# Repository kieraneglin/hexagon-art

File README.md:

# Hexagon Art Piece

Because I'm incapable of saying no to ideas that sound fun

## What is it?

Many tightly packed wooden hexagons, each one driven linearly by its own stepper motor through a scotch yoke, creating a moving effect across the whole piece. A central orchestrator choreographs all of them together over a one-way UART bus.

```
Orchestrator (Raspberry Pi) --UART--> Distributor board --+--> Hexagon unit
                                                            +--> Hexagon unit
                                                            +--> ... (daisy-chained)
```

Each hexagon is a small standalone board: an ATtiny1616, a stepper driver, and an optical endstop for homing. The orchestrator broadcasts movement commands down the bus; units never talk back.

## Why is it?

A local art exhibit asked a communal woodshop that I am part of to create some installations. We were given no requirements other than being told that the theme is "art on the move". I took that extremely literally and this is what I came up with!

## Repository layout

- [`Firmware/`](Firmware/README.md): the per-unit firmware, the UPDI programmer/calibration jig, and the orchestrator software.
- [`Schematic/`](Schematic/README.md): KiCad projects for the hexagon board and the distributor board.
- [`CAD/`](CAD/README.md): the enclosure, mechanism design, and fastener BOM

Each directory's own README has the actual detail; this file is just the map.

## About this repository

This is published as a reference, not a kit. There's no bill-of-materials-to-finished-piece build guide, and no support will be offered. If you're the kind of person who can pick up a KiCad file, a firmware protocol spec, and a CAD model and run with it, everything you need to understand how this works is in here.

## Design philosophy

Because this project is self-funded then donated (and because I bought enough for 80 units), the hexagon units are aggressively cost-optimized. This does introduce compromises in terms of my selected components or communication capabilities (eg: the one-way UART bus), but it's all about tradeoffs.

Besides, I don't expect anyone to actually build this themselves, but I wanted to put it out there in case any of the ideas or techniques might be useful in another context.

## License

Licensed under MIT; see [`LICENSE`](LICENSE). The UPDI programmer builds on [ElTangas/jtag2updi](https://github.com/ElTangas/jtag2updi) (also MIT).

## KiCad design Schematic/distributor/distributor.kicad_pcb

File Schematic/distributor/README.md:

# Distributor plate (v1)

A passive breakout board: two lever-terminal inputs, three JST XH outputs, all six conductors (RX bus, two spares, +12V, GND, +5V) paralleled straight across. No active components, no regulation, nothing to configure. Its job is purely to let a daisy chain branch into more than one direction from a single upstream feed, since the hexagon boards themselves only have one input and one output connector each (see [`../hexagon/README.md`](../hexagon/README.md) for that pinout, which this board mirrors exactly).

## Important note

This board cannot route enough current to power dozens of boards. If you need to do that, you should either solder thicker wires to the board or redesign this PCB.

## Bill of materials

| Ref        | Qty | Part                      | Footprint                                             | MPN             |
| ---------- | --- | ------------------------- | ----------------------------------------------------- | --------------- |
| J1, J2, J5 | 3   | JST XH, 6-pin, horizontal | Connector_JST:JST_XH_S6B-XH-A_1x06_P2.50mm_Horizontal |                 |
| J3, J4     | 2   | Screw terminal, 6-pin     | Connector_Pin:QT06                                    | QT06BDP83H0000G |

Four M3 mounting holes round out the board.

## Files

- `distributor.kicad_pro` / `.kicad_sch` / `.kicad_pcb`: KiCad 10 project.
- `GRBRs.zip`: gerbers and drill files

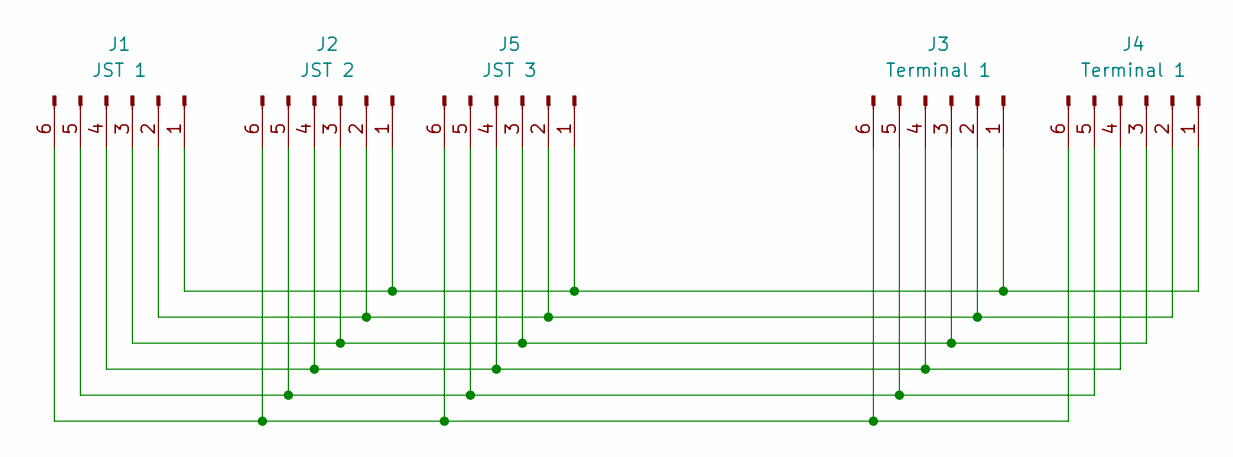
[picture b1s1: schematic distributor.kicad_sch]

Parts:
J1: JST 1; JST_XH_S6B-XH-A_1x06_P2.50mm_Horizontal
J2: JST 2; JST_XH_S6B-XH-A_1x06_P2.50mm_Horizontal
J3, J4: Terminal 1; QT06
J5: JST 3; JST_XH_S6B-XH-A_1x06_P2.50mm_Horizontal

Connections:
unnamed: J1.1, J2.1, J3.1, J4.1, J5.1
unnamed: J1.2, J2.2, J3.2, J4.2, J5.2
unnamed: J1.3, J2.3, J3.3, J4.3, J5.3
unnamed: J1.4, J2.4, J3.4, J4.4, J5.4
unnamed: J1.5, J2.5, J3.5, J4.5, J5.5
unnamed: J1.6, J2.6, J3.6, J4.6, J5.6

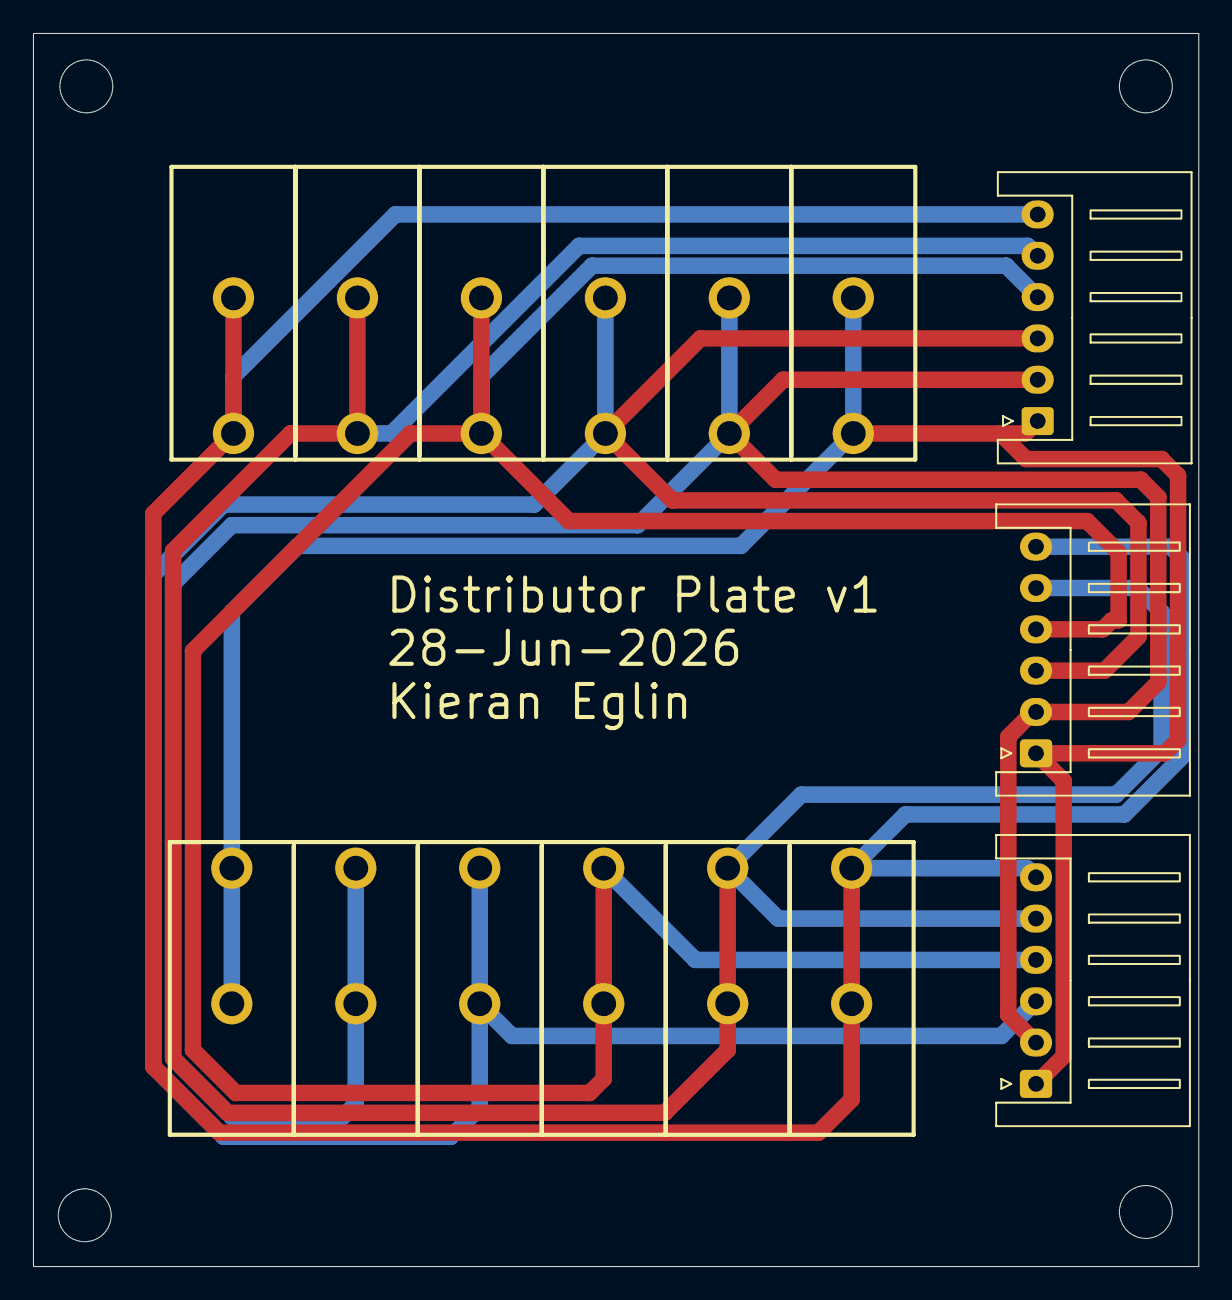
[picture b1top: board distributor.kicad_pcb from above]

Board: 2 copper layers, 70.5 x 74.6 mm, 5 parts (0 on the bottom side), 6 nets.

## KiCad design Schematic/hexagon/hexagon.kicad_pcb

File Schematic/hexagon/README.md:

# Hexagon board (v2)

Per-unit board: one ATtiny1616, a motor driver for the 28BYJ-48, and an optical endstop. Firmware lives at [`../../Firmware/hexagons/`](../../Firmware/hexagons/README.md), which documents the full pin map and communication protocol; this covers the hardware side only.

## Bill of materials

| Ref        | Qty | Value / part                      | Footprint                                           | MPN              |
| ---------- | --- | --------------------------------- | --------------------------------------------------- | ---------------- |
| U3         | 1   | ATtiny1616-MN                     | VQFN-20-1EP, 3x3mm, 0.4mm pitch                     | ATtiny1616-MN    |
| U2         | 1   | TPL7407L                          | TSSOP-16                                            | TPL7407LAQPWRQ1  |
| PI1        | 1   | Optical interrupter               | LiteOn LTH-301-07                                   | LTH-301-07       |
| D1         | 1   | Schottky diode                    | SOD-123W                                            | PMEG2010ER,115   |
| D2         | 1   | Status LED                        | 0805                                                | 5988110107F      |
| C2         | 1   | 10uF                              | 0805                                                | C0805C106K8PACTU |
| C1, C3, C5 | 3   | 100nF                             | 0805                                                | CL21B104KACNNNC  |
| C4         | 1   | 220uF                             | 6.3x7.7mm electrolytic                              | UCM1E221MCL1GS   |
| R4         | 1   | 4.7k                              | 0805                                                | RC0805FR-074K7L  |
| R2, R3, R6 | 3   | 220 ohm                           | 0805                                                | RC0805FR-07220RL |
| J1, J2     | 2   | JST XH, 6-pin, vertical           | Connector_JST:JST_XH_B6B-XH-A_1x06_P2.50mm_Vertical | (JST)            |
| J4         | 1   | JST XH, 5-pin, vertical (motor)   | Connector_JST:JST_XH_B5B-XH-A_1x05_P2.50mm_Vertical | (JST)            |
| J5         | 1   | 6-pin socket (GPIO breakout)      | PinSocket_1x06_P2.54mm_Vertical                     |                  |
| J6         | 1   | 8-pin socket (programming header) | PinSocket_2x04_P2.54mm_Vertical                     |                  |
| J7         | 1   | 2-pin header (spare passthrough)  | PinHeader_1x02_P2.54mm_Vertical                     |                  |

Not on this board: the 28BYJ-48 motor itself, which connects via `J4`.

`BOM.csv` in this directory is the raw KiCad-generated export; it collapses several unrelated connectors and the MCU into a single row with no part number, which is why the table above is organized per reference instead.

## Connectors

**J1 (in) / J2 (out)**, the daisy-chain, 6-pin JST XH, identical pinout on both:

| Pin | Signal   |
| --- | -------- |
| 1   | RX (bus) |
| 2   | spare    |
| 3   | spare    |
| 4   | +12V     |
| 5   | GND      |
| 6   | +5V      |

Pins 2-3 also passthrough to `J7`, a 2-pin header for a future sensor or accessory tap.

**J4**, motor (5-pin JST XH): pins 1-4 are the driver outputs to the 28BYJ-48's four coils, pin 5 is +12V.

**J5**, GPIO breakout (6-pin socket): PA1, PA2, PA3, PA7, PB4, PB5, unused by the current firmware.

**J6**, programming header (8-pin socket):

| Pin  | Signal                             |
| ---- | ---------------------------------- |
| 1, 2 | GND                                |
| 3, 4 | +5V                                |
| 5    | UPDI                               |
| 6    | TX                                 |
| 7    | PA6 (oscillator calibration input) |
| 8    | RX                                 |

This is what the programmer jig (`../../Firmware/programmer/`) connects to.

## MCU pin map

| Pin                          | Net                                       |
| ---------------------------- | ----------------------------------------- |
| PC0-PC3                      | Motor driver inputs (to `U2`)             |
| PB0                          | Endstop (`PI1`, active low)               |
| PB1                          | Status LED                                |
| PB2                          | UART TX                                   |
| PB3                          | UART RX                                   |
| PA0                          | UPDI                                      |
| PA6                          | Oscillator calibration input (`J6` pin 7) |
| PA1, PA2, PA3, PA7, PB4, PB5 | Broken out on `J5`, unused                |

## Power

+5V arrives through `D1` (series Schottky) before reaching the local rail, isolating the board's own supply from the daisy chain so that reprogramming one unit in place can't back-power its neighbors. +12V feeds `U2`'s COM pin and the motor directly, with no local regulation of either rail.

The `D1` diode is to prevent back-powering the local +5V rail from the daisy chain if you're reprogramming the board in place.

## Files

- `hexagon.kicad_pro` / `.kicad_sch` / `.kicad_pcb`: KiCad 10 project.
- `GRBRs.zip`: gerbers and drill files
- `BOM.csv`: raw KiCad BOM export.

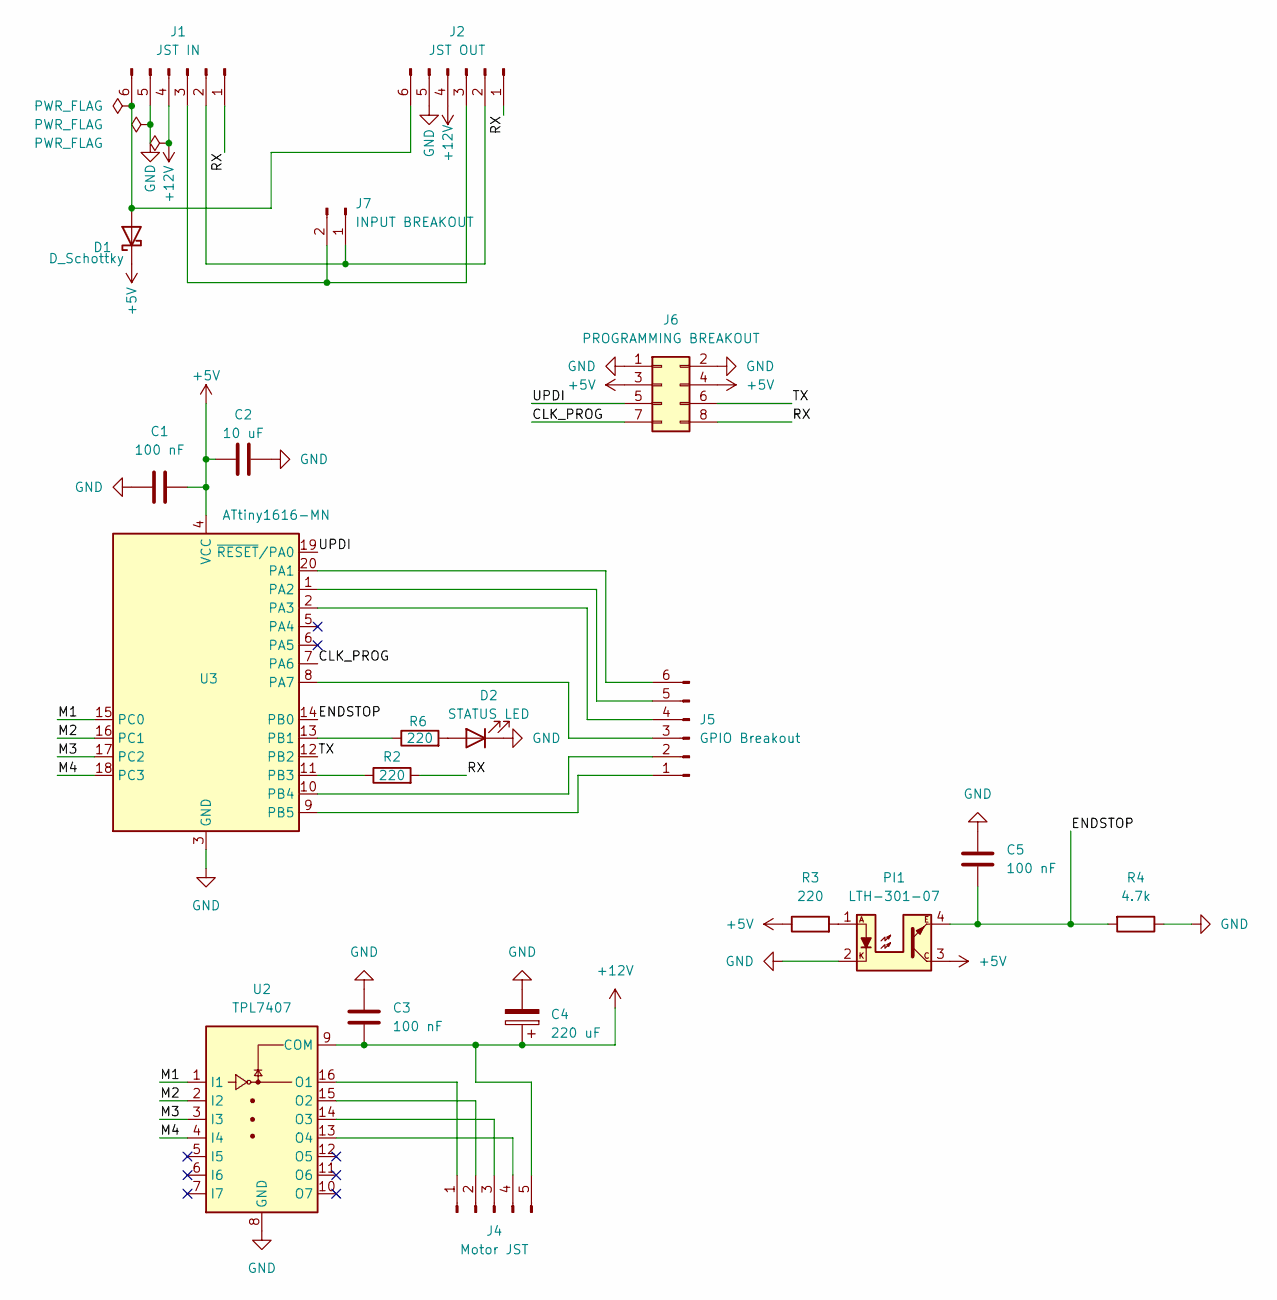
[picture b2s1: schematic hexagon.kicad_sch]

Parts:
C1, C3, C5: 100 nF; C_0805_2012Metric_Pad1.18x1.45mm_HandSolder
C2: 10 uF; C_0805_2012Metric_Pad1.18x1.45mm_HandSolder
C4: 220 uF; CP_Elec_6.3x7.7
D1: D_Schottky; Nexperia_CFP3_SOD-123W
D2: STATUS LED; LED_0805_2012Metric_Pad1.15x1.40mm_HandSolder
J1: JST IN; JST_XH_B6B-XH-A_1x06_P2.50mm_Vertical
J2: JST OUT; JST_XH_B6B-XH-A_1x06_P2.50mm_Vertical
J4: Motor JST; JST_XH_B5B-XH-A_1x05_P2.50mm_Vertical
J5: GPIO Breakout; PinSocket_1x06_P2.54mm_Vertical
J6: PROGRAMMING BREAKOUT
J7: INPUT BREAKOUT; PinHeader_1x02_P2.54mm_Vertical
PI1: LTH-301-07; LiteOn_LTH-301-07
R2, R3, R6: 220; R_0805_2012Metric_Pad1.20x1.40mm_HandSolder
R4: 4.7k; R_0805_2012Metric_Pad1.20x1.40mm_HandSolder
U2: TPL7407; TSSOP-16_4.4x5mm_P0.65mm
U3: ATtiny1616-MN; VQFN-20-1EP_3x3mm_P0.4mm_EP1.7x1.7mm

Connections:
+5V: C1.2, C2.2, D1.1 (K), J6.3, J6.4, PI1.3, R3.1, U3.4 (VCC)
+12V: C3.2, C4.1, J1.4, J2.4, J4.5, U2.9 (COM)
/CLK_PROG: J6.7, U3.7 (PA6)
/ENDSTOP: C5.2, PI1.4, R4.2, U3.14 (PB0)
/M1: U2.1 (I1), U3.15 (PC0)
/M2: U2.2 (I2), U3.16 (PC1)
/M3: U2.3 (I3), U3.17 (PC2)
/M4: U2.4 (I4), U3.18 (PC3)
/RX: J1.1, J2.1, J6.8, R2.2
/TX: J6.6, U3.12 (PB2)
/UPDI: J6.5, U3.19 (~RESET/PA0)
GND: C1.1, C2.1, C3.1, C4.2, C5.1, D2.1 (K), J1.5, J2.5, J6.1, J6.2, PI1.2, R4.1, U2.8 (GND), U3.3 (GND), U3.21 (GND)
unnamed: D1.2 (A), J1.6, J2.6
unnamed: D2.2 (A), R6.2
unnamed: J1.2, J2.2, J7.1
unnamed: J1.3, J2.3, J7.2
unnamed: J4.1, U2.16 (O1)
unnamed: J4.2, U2.15 (O2)
unnamed: J4.3, U2.14 (O3)
unnamed: J4.4, U2.13 (O4)
unnamed: J5.1, U3.9 (PB5)
unnamed: J5.2, U3.10 (PB4)
unnamed: J5.3, U3.8 (PA7)
unnamed: J5.4, U3.2 (PA3)
unnamed: J5.5, U3.1 (PA2)
unnamed: J5.6, U3.20 (PA1)
unnamed: PI1.1, R3.2
unnamed: R6.1, U3.13 (PB1)
unnamed: R2.1, U3.11 (PB3)

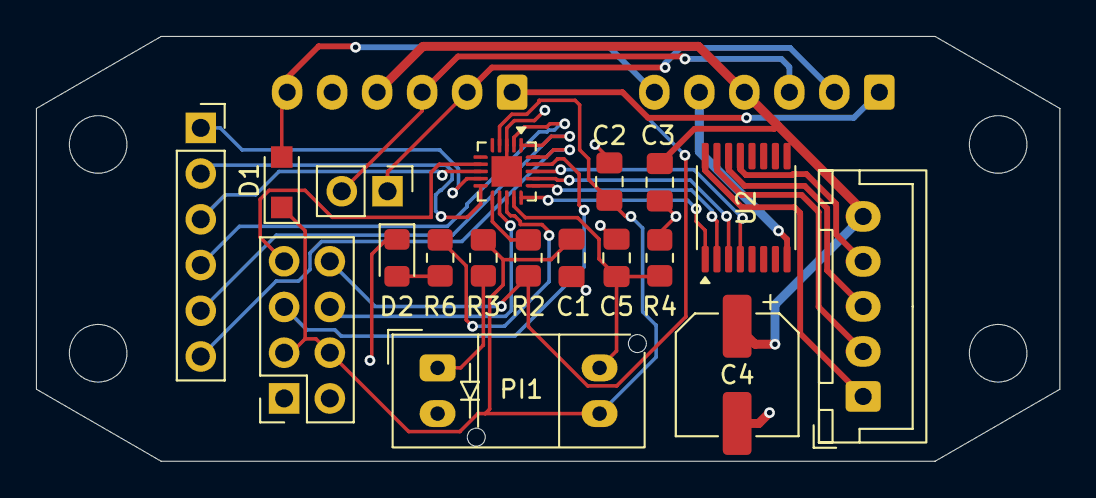
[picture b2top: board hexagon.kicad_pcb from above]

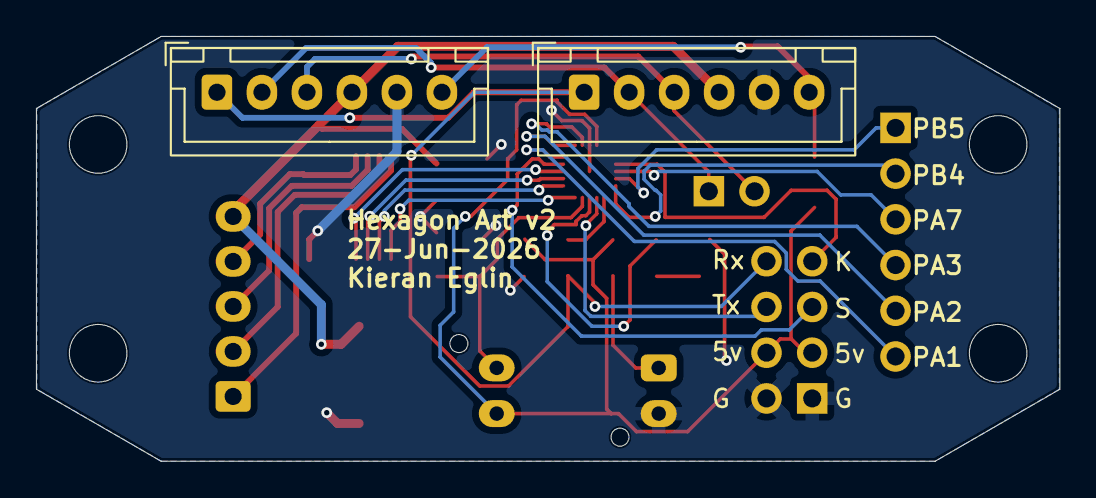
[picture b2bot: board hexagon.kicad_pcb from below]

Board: 2 copper layers, 56.9 x 23.6 mm, 20 parts (2 on the bottom side), 29 nets.

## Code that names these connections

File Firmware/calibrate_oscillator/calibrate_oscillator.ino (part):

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// megaTinyTuner (megaTinyCore), simplified for our single-target use case:
//
//   1. An Arduino Uno running the 500HzReference sketch outputs a 500 Hz square
//      wave on pin 9. This signal is connected to PA6 on the ATtiny1616.
//      The Uno's crystal oscillator (±50ppm typical) is our timebase.
//
//   2. The ATtiny1616's main clock is set to /4 prescale so the CPU can safely
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// --------------------------------------
//
//   Arduino Uno GND  ────→  ATtiny1616 GND
//   Arduino Uno Pin 9 ────→  ATtiny1616 PA6
//   Arduino Uno 5V   ────→  ATtiny1616 VDD  [optional]
//
//   On a populated hexagon board (VQFN-20), PA6 and GND/VDD are already
//   broken out on the J6 programming header — see ../programmer/README.md
//   for that pinout and for running the 500 Hz reference from the
//   programmer jig itself instead of a separate Uno.
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//   first, then move the board to the calibration jig (Uno providing power +
//   500 Hz signal).
//
// STATUS LED INDICATION (PB1)
// ---------------------------
//   Power on:   LED off (during setup)
//   Cal start:  3 slow blinks (200ms on, 200ms off) → entering measurement
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// WHAT THE CALIBRATION JIG OPERATOR SEES
// --------------------------------------
//   1. Flash this sketch to the ATtiny1616 via UPDI.
//   2. Move the board to the calibration jig (powered by Uno, 500Hz on PA6).
//   3. LED blinks 3 times slowly (~1 second) → measurement starts.
//   4. LED flickers for ~2 seconds while 64 OSCCAL values are tested.
//   5. LED goes solid ON → calibration success. Board is done.
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// ---------------------------------------------------------------------------

// 500 Hz reference input from Arduino Uno pin 9.
// PA6 is unused by the hexagon firmware itself: stepper uses PC0-3,
// endstop uses PB0, status LED uses PB1, UART uses PB2/PB3, UPDI uses
// PA0. PA6 is broken out on the J6 programming header specifically so
// it's reachable for this calibration step.
#define TUNING_PIN PIN_PA6

// Status LED — same pin the hexagon firmware uses (PB1).
#define STATUS_LED PIN_PB1

// ---------------------------------------------------------------------------
// Calibration parameters
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
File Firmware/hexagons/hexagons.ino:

#include "clockcal.h"
#include "comm.h"
#include "homing.h"
#include "optical_switch.h"
#include "runner.h"
#include "stepper.h"

Stepper28BYJ motor(PIN_PC0, PIN_PC1, PIN_PC2, PIN_PC3);
OpticalSwitch endstop(PIN_PB0);

static const uint8_t statusLedPin = PIN_PB1;

void setup() {
  delay(250);  // Ensure stability when testing
  clockcalBegin();
  commBegin(115200);
  clockcalPrintDiag();
  uint8_t addr = commReadAddressFromEEPROM();
  commSetAddress(addr);

  endstop.begin();

  motor.begin();
  motor.setRPM(14.5f);  // minimises resonance on 28BYJ-48 at this gear ratio

  randomSeed(addr);  // per-unit seed so the stagger below actually differs across units
  delay((uint16_t)(random(1000)));  // stagger motor startup load across units

  homeMotor(motor, endstop);
  motor.resetAngle();

  // Deferred until well after boot — see clockcal.h for why writing NVM
  // (USERROW/EEPROM) right at power-on risks corruption on this hardware.
  clockcalCommit();

  runnerBegin(motor, endstop);
}

void loop() {
  runnerUpdate();

  if (endstop.isTriggered()) {
    digitalWrite(statusLedPin, HIGH);
  } else {
    digitalWrite(statusLedPin, LOW);
  }
}
